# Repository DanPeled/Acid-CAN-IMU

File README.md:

# Acid CAN IMU
> A CAN Based IMU utilizing the BNO080 IMU

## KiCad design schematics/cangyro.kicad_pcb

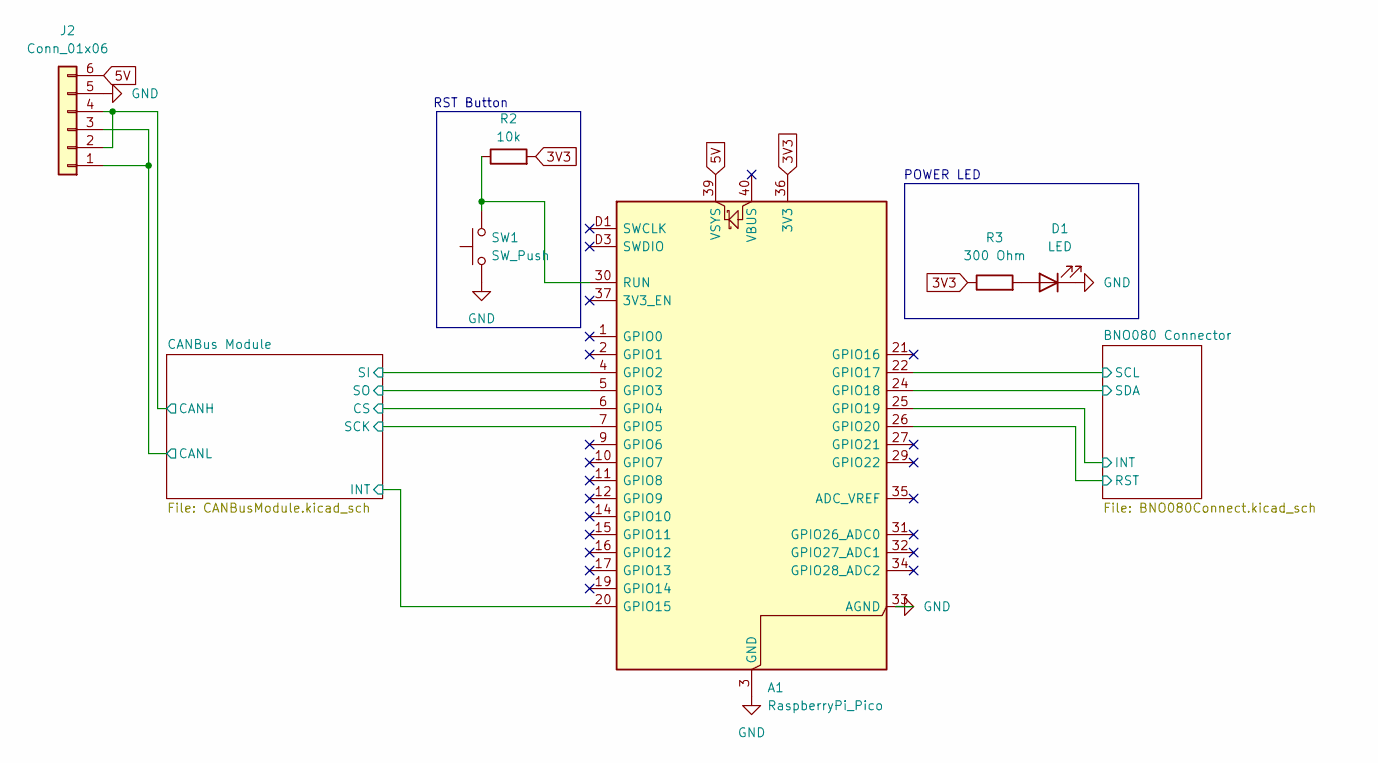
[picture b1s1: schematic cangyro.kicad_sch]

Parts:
A1: RaspberryPi_Pico; RaspberryPi_Pico_SMD_HandSolder
D1: LED; LED_0603_1608Metric
J2: Conn_01x06; TerminalBlock_Phoenix_MKDS-1,5-6_1x06_P5.00mm_Horizontal
R2: 10k; R_0603_1608Metric
R3: 300 Ohm; R_0603_1608Metric
SW1: SW_Push; SW_Push_1P1T_NO_CK_KMR2

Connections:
3V3: A1.36 (3V3), R2.2, R3.1; also elsewhere on the board
5V: A1.39 (VSYS), J2.6; also elsewhere on the board
/BNO080 Connector/INT: A1.25 (GPIO19); also elsewhere on the board
/BNO080 Connector/RST: A1.26 (GPIO20); also elsewhere on the board
/BNO080 Connector/SCL: A1.22 (GPIO17); also elsewhere on the board
/BNO080 Connector/SDA: A1.24 (GPIO18); also elsewhere on the board
/CANBus Module/CANH: J2.2, J2.4; also elsewhere on the board
/CANBus Module/CANL: J2.1, J2.3; also elsewhere on the board
/CANBus Module/CS: A1.6 (GPIO4); also elsewhere on the board
/CANBus Module/INT: A1.20 (GPIO15); also elsewhere on the board
/CANBus Module/SCK: A1.7 (GPIO5); also elsewhere on the board
/CANBus Module/SI: A1.4 (GPIO2); also elsewhere on the board
/CANBus Module/SO: A1.5 (GPIO3); also elsewhere on the board
GND: A1.3 (GND), A1.8 (GND), A1.13 (GND), A1.18 (GND), A1.23 (GND), A1.28 (GND), A1.33 (AGND), A1.38 (GND), A1.D2 (GND), D1.1 (K), J2.5, SW1.1; also elsewhere on the board
unnamed: A1.30 (RUN), R2.1, SW1.2
unnamed: D1.2 (A), R3.2

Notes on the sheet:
POWER LED
RST Button

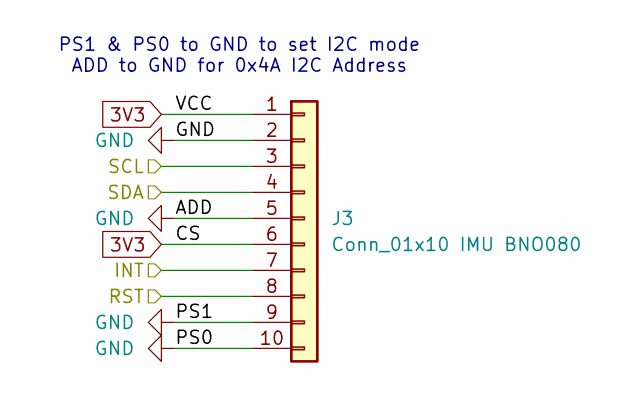
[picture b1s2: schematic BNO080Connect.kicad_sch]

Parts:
J3: Conn_01x10 IMU BNO080; PinSocket_1x10_P1.00mm_Vertical

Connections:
3V3: J3.1, J3.6; also elsewhere on the board
/BNO080 Connector/INT: J3.7; also elsewhere on the board
/BNO080 Connector/RST: J3.8; also elsewhere on the board
/BNO080 Connector/SCL: J3.3; also elsewhere on the board
/BNO080 Connector/SDA: J3.4; also elsewhere on the board
GND: J3.2, J3.5, J3.9, J3.10; also elsewhere on the board

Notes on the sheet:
PS1 & PS0 to GND to set I2C mode ADD to GND for 0x4A I2C Address

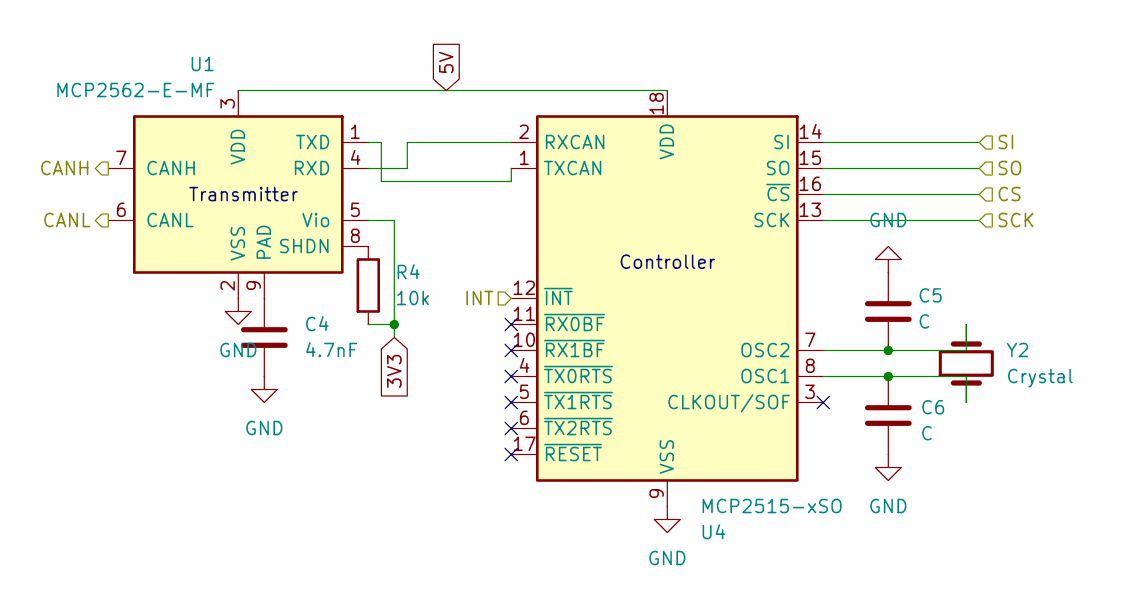
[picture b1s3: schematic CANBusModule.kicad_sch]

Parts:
C4: 4.7nF; C_0603_1608Metric
C5, C6: C; C_0603_1608Metric
R4: 10k; R_0603_1608Metric
U1: MCP2562-E-MF; DFN-8-1EP_3x3mm_P0.65mm_EP1.55x2.4mm
U4: MCP2515-xSO; SOIC-18W_7.5x11.6mm_P1.27mm
Y2: Crystal; Crystal_HC49-U-3Pin_Vertical

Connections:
3V3: R4.2, U1.5 (Vio); also elsewhere on the board
5V: U1.3 (VDD), U4.18 (VDD); also elsewhere on the board
/CANBus Module/CANH: U1.7 (CANH); also elsewhere on the board
/CANBus Module/CANL: U1.6 (CANL); also elsewhere on the board
/CANBus Module/CS: U4.16 (~CS); also elsewhere on the board
/CANBus Module/INT: U4.12 (~INT); also elsewhere on the board
/CANBus Module/SCK: U4.13 (SCK); also elsewhere on the board
/CANBus Module/SI: U4.14 (SI); also elsewhere on the board
/CANBus Module/SO: U4.15 (SO); also elsewhere on the board
GND: C4.2, C5.1, C6.2, U1.2 (VSS), U4.9 (VSS); also elsewhere on the board
unnamed: C4.1, U1.9 (PAD)
unnamed: U1.4 (RXD), U4.2 (RXCAN)
unnamed: R4.1, U1.8 (SHDN)
unnamed: U1.1 (TXD), U4.1 (TXCAN)
unnamed: C6.1, U4.8 (OSC1), Y2.1
unnamed: C5.2, U4.7 (OSC2), Y2.2

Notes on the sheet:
Controller
Transmitter

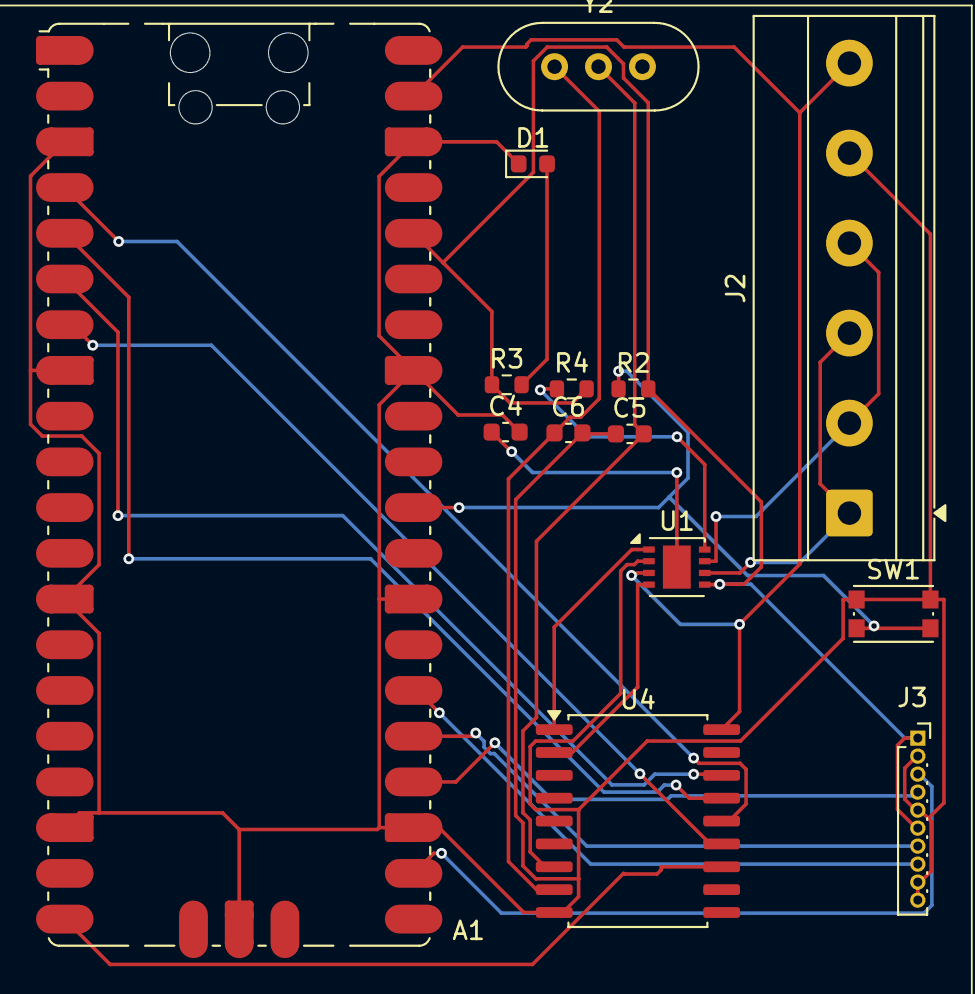
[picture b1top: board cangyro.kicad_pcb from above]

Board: 2 copper layers, 14 parts (0 on the bottom side), 22 nets.

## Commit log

2026-06-06 Base Schematics
2026-06-07 Base software project
2026-06-08 Replaced STM Microcontroller with PiPico, base code and new schematics
2026-06-08 Switched MicroController To PiPco
    - Base software with BNO08x lib and pico stuff
2026-06-08 Added Footprints
2026-06-08 Routing PCB with FreeRouting
2026-06-08 Routing PCB with FreeRouting (#2)
2026-06-08 Basic Interaction with the MCP2515 and better BNO080 lbi
2026-06-08 Basic Interaction with the MCP2515 and better BNO080 lbi (#3)
2026-06-09 Exposing GetTemperature, Switched to using Quanternions
2026-06-10 Switched to "game" data, cleaner main - Using game vectors and rotation instead of absolute to be true to the field and not to the earth itself (why would i even want that and either way that would c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
